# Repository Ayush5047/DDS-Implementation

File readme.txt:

The project is on low cost implementation of function generator using direct digital systhesis technology.

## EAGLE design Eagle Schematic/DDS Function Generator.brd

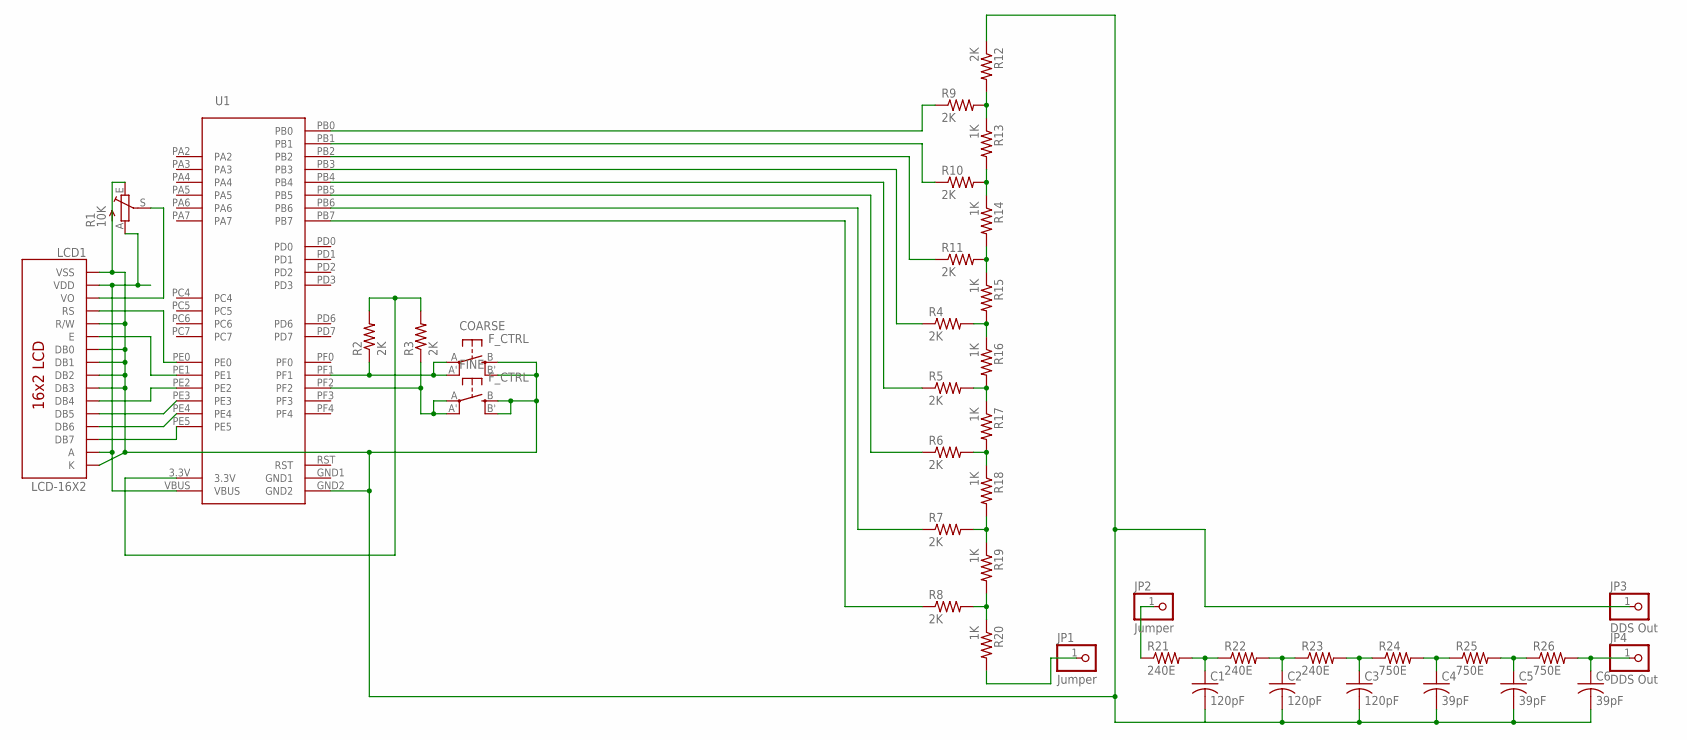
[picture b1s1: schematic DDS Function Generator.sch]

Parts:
C1, C2, C3: 120pF; C0805
C4, C5, C6: 39pF; C0603
COARSE: F_CTRL; EVQ-Q2
FINE: F_CTRL; EVQ-Q2
JP1, JP2: Jumper; 1X01
JP3, JP4: DDS Out; 1X01
LCD1: LCD-16X2; LCD-16X2_NOHOLESNOSILK
R1: 10K; B25P
R2, R3, R4, R5, R6, R7, R8, R9, R10, R11, R12: 2K; R1206
R13, R14, R15, R16, R17, R18, R19, R20: 1K; R1206
R21, R22, R23: 240E; R1206
R24, R25, R26: 750E; R1206
U1: U1; LAUNCHPAD-XL

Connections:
3V3: R2.2, R3.2, U1.3.3V
GND: C1.2, C2.2, C3.2, C4.2, C5.2, C6.2, COARSE.B (S), COARSE.B' (S1), FINE.B (S), FINE.B' (S1), JP3.1, LCD1.1 (VSS), LCD1.5 (R/W), LCD1.7 (DB0), LCD1.8 (DB1), LCD1.9 (DB2), LCD1.10 (DB3), LCD1.16 (K), R1.E, R12.1, U1.GND2
unnamed: R7.1, U1.PB6
unnamed: R9.2, R12.2, R13.1
unnamed: R10.2, R13.2, R14.1
unnamed: R11.2, R14.2, R15.1
unnamed: R9.1, U1.PB0
unnamed: R4.2, R15.2, R16.1
unnamed: R10.1, U1.PB1
unnamed: R11.1, U1.PB2
unnamed: R5.2, R16.2, R17.1
unnamed: R6.2, R17.2, R18.1
unnamed: R7.2, R18.2, R19.1
unnamed: R8.2, R19.2, R20.1
unnamed: R4.1, U1.PB3
unnamed: R5.1, U1.PB4
unnamed: R6.1, U1.PB5
unnamed: R8.1, U1.PB7
unnamed: COARSE.A, COARSE.A' (P1), R2.1, U1.PF1
unnamed: JP1.1, R20.2
unnamed: C1.1, R21.2, R22.1
unnamed: C2.1, R22.2, R23.1
unnamed: C3.1, R23.2, R24.1
unnamed: C4.1, R24.2, R25.1
unnamed: C5.1, R25.2, R26.1
unnamed: C6.1, JP4.1, R26.2
unnamed: FINE.A, FINE.A' (P1), R3.1, U1.PF2
unnamed: LCD1.2 (VDD), LCD1.15 (A), R1.A, U1.VBUS
unnamed: LCD1.4 (RS), U1.PE0
unnamed: LCD1.6 (E), U1.PE1
unnamed: LCD1.12 (DB5), U1.PE3
unnamed: LCD1.13 (DB6), U1.PE4
unnamed: LCD1.14 (DB7), U1.PE5
unnamed: LCD1.3 (VO), R1.S
unnamed: JP2.1, R21.1
unnamed: LCD1.11 (DB4), U1.PE2
RST: U1.RST

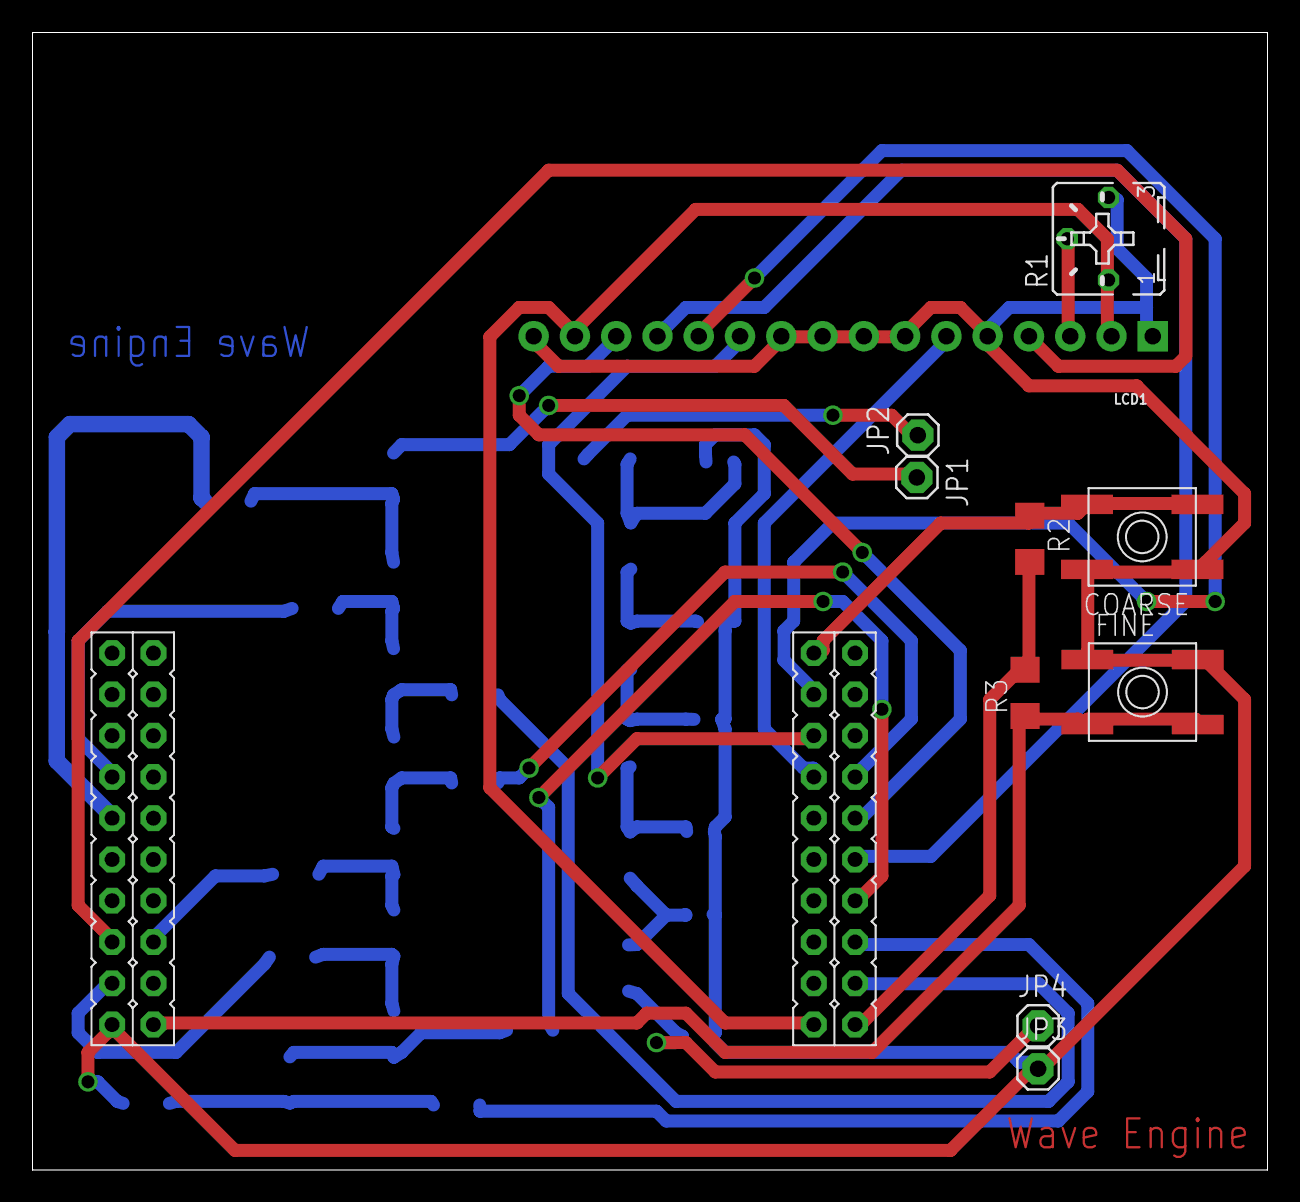
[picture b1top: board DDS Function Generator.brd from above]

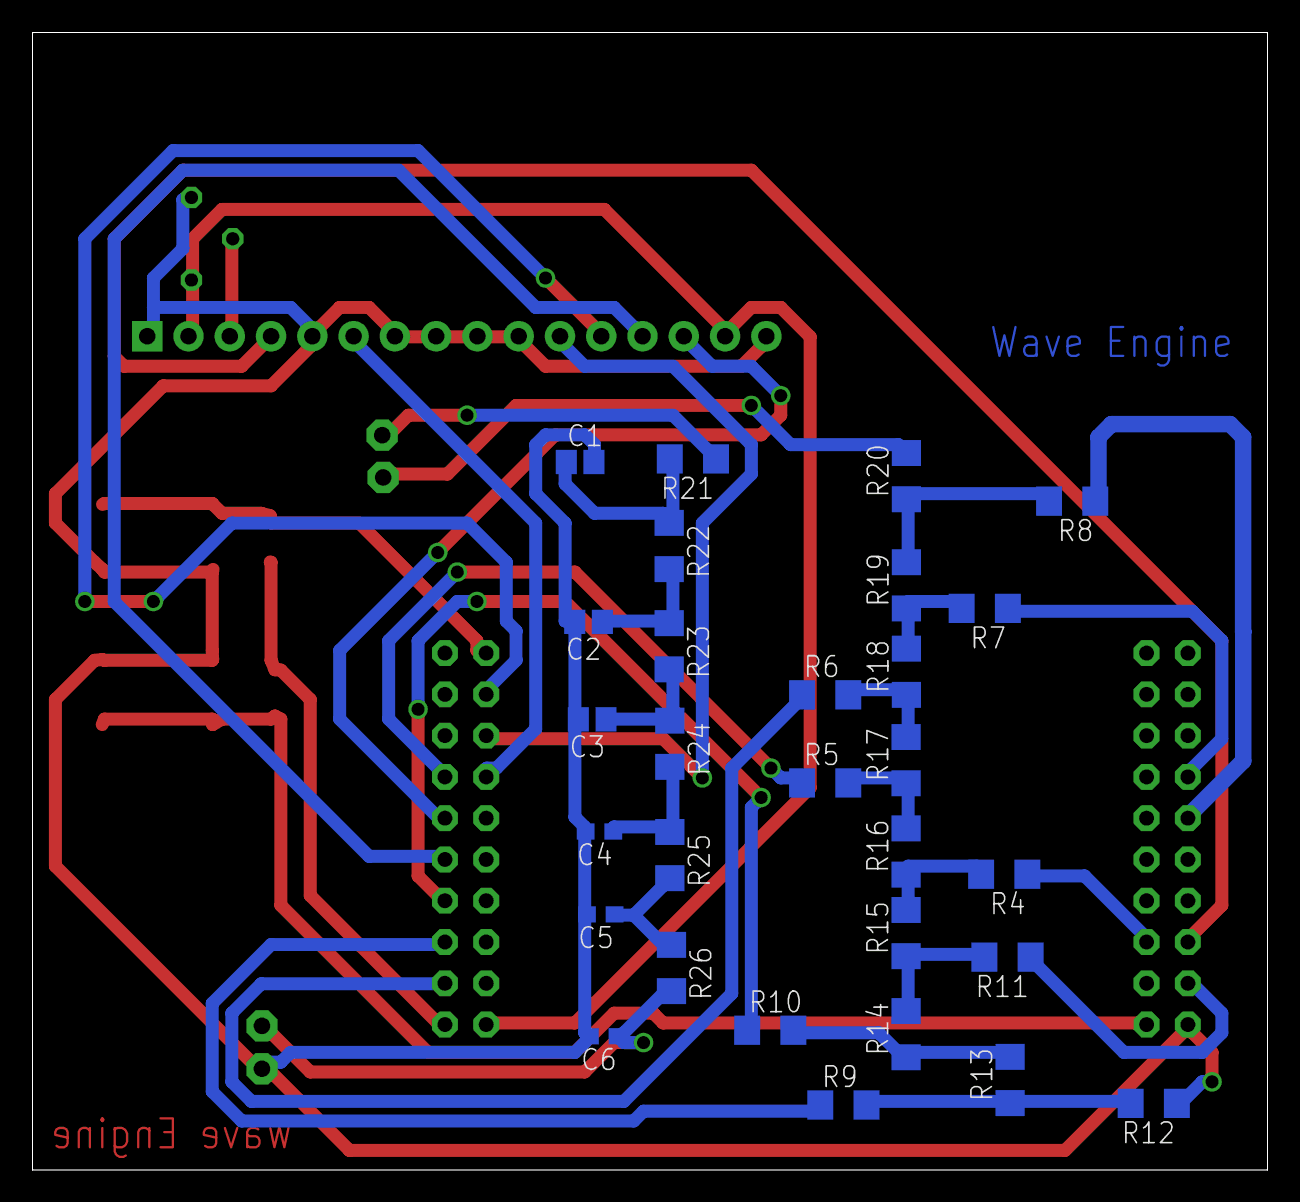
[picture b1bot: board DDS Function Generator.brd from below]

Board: 2 copper layers, 76.0 x 70.0 mm, 40 parts (29 on the bottom side), 36 nets.

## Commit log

2017-10-12 Atmega 32 Timer based Logic
2017-10-15 C Code for generating Sine samples
2017-10-18 Tiva Based Code
2017-10-22 LCD INTERFACED
2017-10-25 Wave Generated
2017-10-26 Lcd Interfaced at PORTE
2017-10-26 lib formed
2017-10-27 Interface Created
2017-10-27 Work Continued
2017-10-29 Seperate Files Created
2017-10-29 Efficiency Increased 37%
2017-11-02 New experiments
2017-11-05 New experiments Added
2017-11-09 Python Code And Eagle Schematic Added

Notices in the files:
parts and their libraries:
SparkFun-Displays: Licensing: Creative Commons ShareAlike 4.0 International - https://creativecommons.org/licenses/by-sa/4.0
